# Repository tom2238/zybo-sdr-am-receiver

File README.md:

Digilent ZYBO, SDR AM radio
================

SDR AM receiver on development board Digilent ZYBO. School project.

Software:
* Vivado 2014.4
* Xilinx SDK 2014.4

Part: xc7z010clg400-1

Directories:
* _audio_sample - recorded audio from SDR
* _eagle - matrix keyboard and amplifier schematic (without LCD and power supply)

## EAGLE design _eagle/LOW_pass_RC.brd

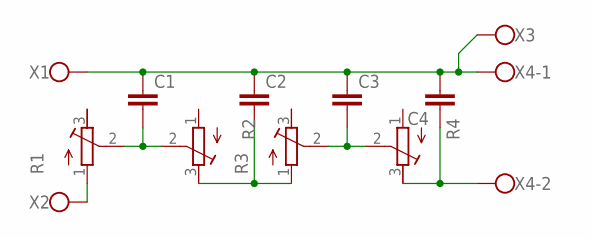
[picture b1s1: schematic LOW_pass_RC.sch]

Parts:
C1, C2, C3, C4: C-EU050-030X075; C050-030X075
R1, R2, R3, R4: R-TRIMM64W; RTRIM64W
X1, X2, X3: W237-112
X4: W237-102

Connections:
unnamed: C1.1, C2.1, C3.1, C4.2, X1.1, X3.1, X4.1
unnamed: R1.1 (A), X2.1
unnamed: C1.2, R1.2 (S), R2.2 (S)
unnamed: C2.2, R2.3 (E), R3.1 (A)
unnamed: C3.2, R3.2 (S), R4.2 (S)
unnamed: C4.1, R4.3 (E), X4.2

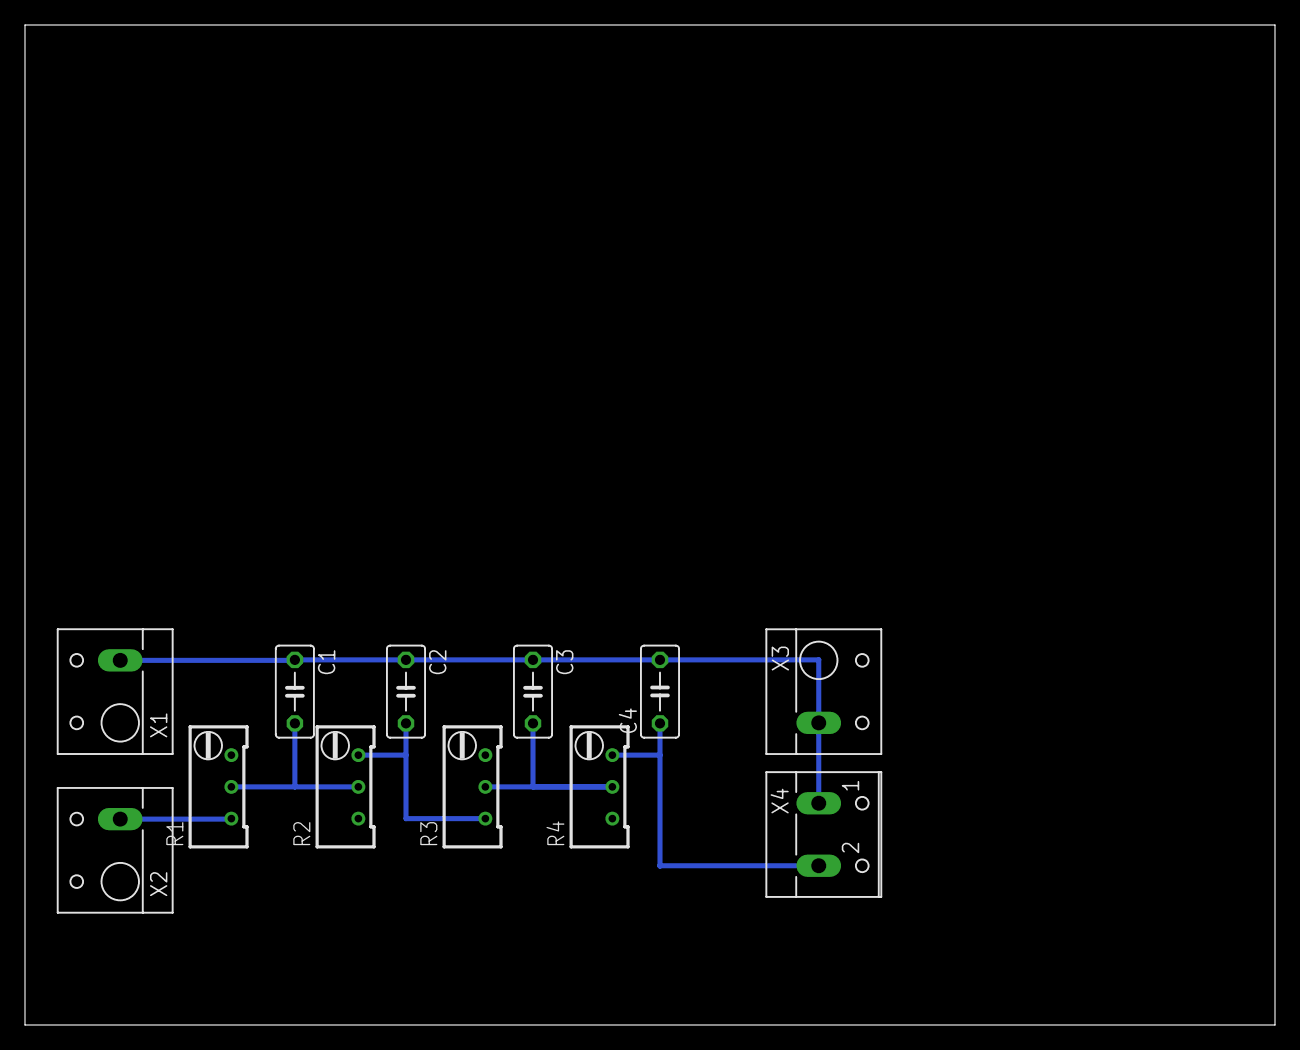
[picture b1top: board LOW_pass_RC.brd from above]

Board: 2 copper layers, 100.0 x 80.0 mm, 12 parts (0 on the bottom side), 6 nets.

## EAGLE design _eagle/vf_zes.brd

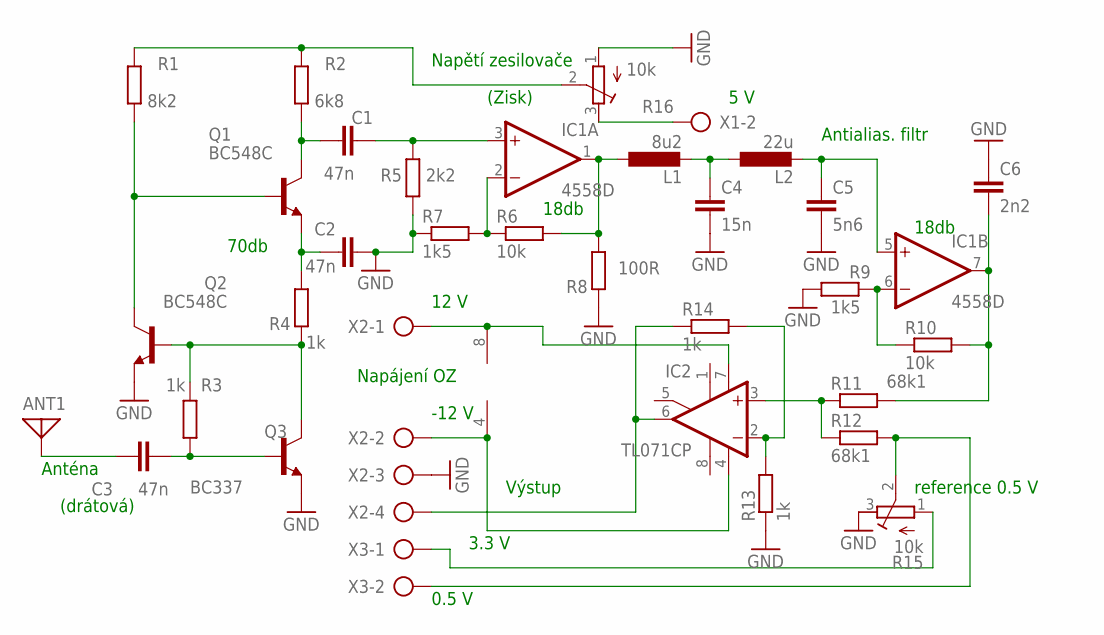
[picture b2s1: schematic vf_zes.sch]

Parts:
ANT1: ANTENNA; PAD-01
C1, C2, C3: 47n; C025-025X050
C4: 15n; C050-025X075
C5: 5n6; C050-025X075
C6: 2n2; C050-030X075
IC1: 4558D; DIL08
IC2: TL071CP; DIL08
L1: 8u2; 0207/12
L2: 22u; 0207/12
Q1, Q2: BC548C; TO92-EBC
Q3: BC337; TO92-EBC
R1: 8k2; 0207/10
R2: 6k8; 0207/10
R3, R4: 1k; 0207/10
R5: 2k2; 0207/10
R6, R10: 10k; 0207/10
R7, R9: 1k5; 0207/10
R8: 100R; 0207/10
R11, R12: 68k1; 0309/12
R13, R14: 1k; 0309/12
R15: 10k; RTRIM64W
R16: 10k; RTRIM64X
X1: AK300/2
X2: AK500/4-H
X3: AK500/2-H

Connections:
GND: C2.2, C4.2, C5.2, C6.1, Q2.E, Q3.E, R5.1, R7.1, R8.1, R9.1, R13.1, R15.3 (A), R16.1 (A), X2.3
unnamed: Q1.B, Q2.C, R1.1
unnamed: C1.1, Q1.C, R2.1
unnamed: C2.1, Q1.E, R4.2
unnamed: R1.2, R2.2, R16.2 (S)
unnamed: Q2.B, Q3.C, R3.1, R4.1
unnamed: C3.2, Q3.B, R3.2
unnamed: C1.2, IC1.3 (+IN), R5.2
unnamed: ANT1.1, C3.1
unnamed: IC1.2 (-IN), R6.1, R7.2
unnamed: IC1.1 (OUT), L1.1, R6.2, R8.2
unnamed: C4.1, L1.2, L2.1
unnamed: C5.1, IC1.5 (+IN), L2.2
unnamed: IC1.6 (-IN), R9.2, R10.1
unnamed: C6.2, IC1.7 (OUT), R10.2, R11.2
unnamed: IC2.3 (+IN), R11.1, R12.1
unnamed: R12.2, R15.2 (S), X3.2
unnamed: IC2.2 (-IN), R13.2, R14.2
unnamed: IC2.6 (OUT), R14.1, X2.4
unnamed: R15.1 (E), X3.1
unnamed: IC1.8 (V+), IC2.7 (V+), X2.1
unnamed: IC1.4 (V-), IC2.4 (V-), X2.2
unnamed: R16.3 (E), X1.2

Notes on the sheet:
Napájení OZ
reference 0.5 V
3.3 V
5 V
Výstup
0.5 V
-12 V
12 V
Anténa
Napětí zesilovače
Antialias. filtr
(Zisk)
(drátová)
70db
18db

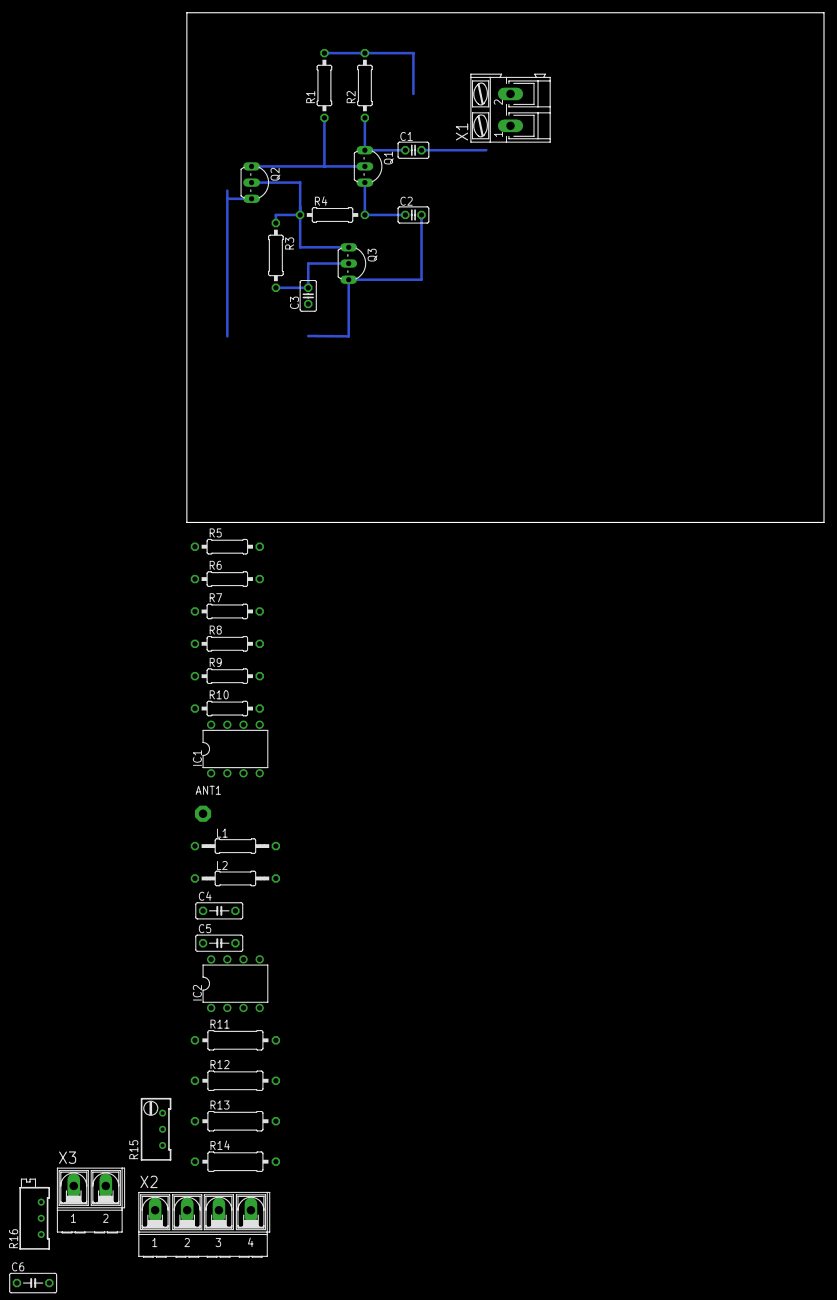
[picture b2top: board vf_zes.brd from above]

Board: 2 copper layers, 100.0 x 80.0 mm, 33 parts (0 on the bottom side), 23 nets.

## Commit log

2018-08-03 Initial release
